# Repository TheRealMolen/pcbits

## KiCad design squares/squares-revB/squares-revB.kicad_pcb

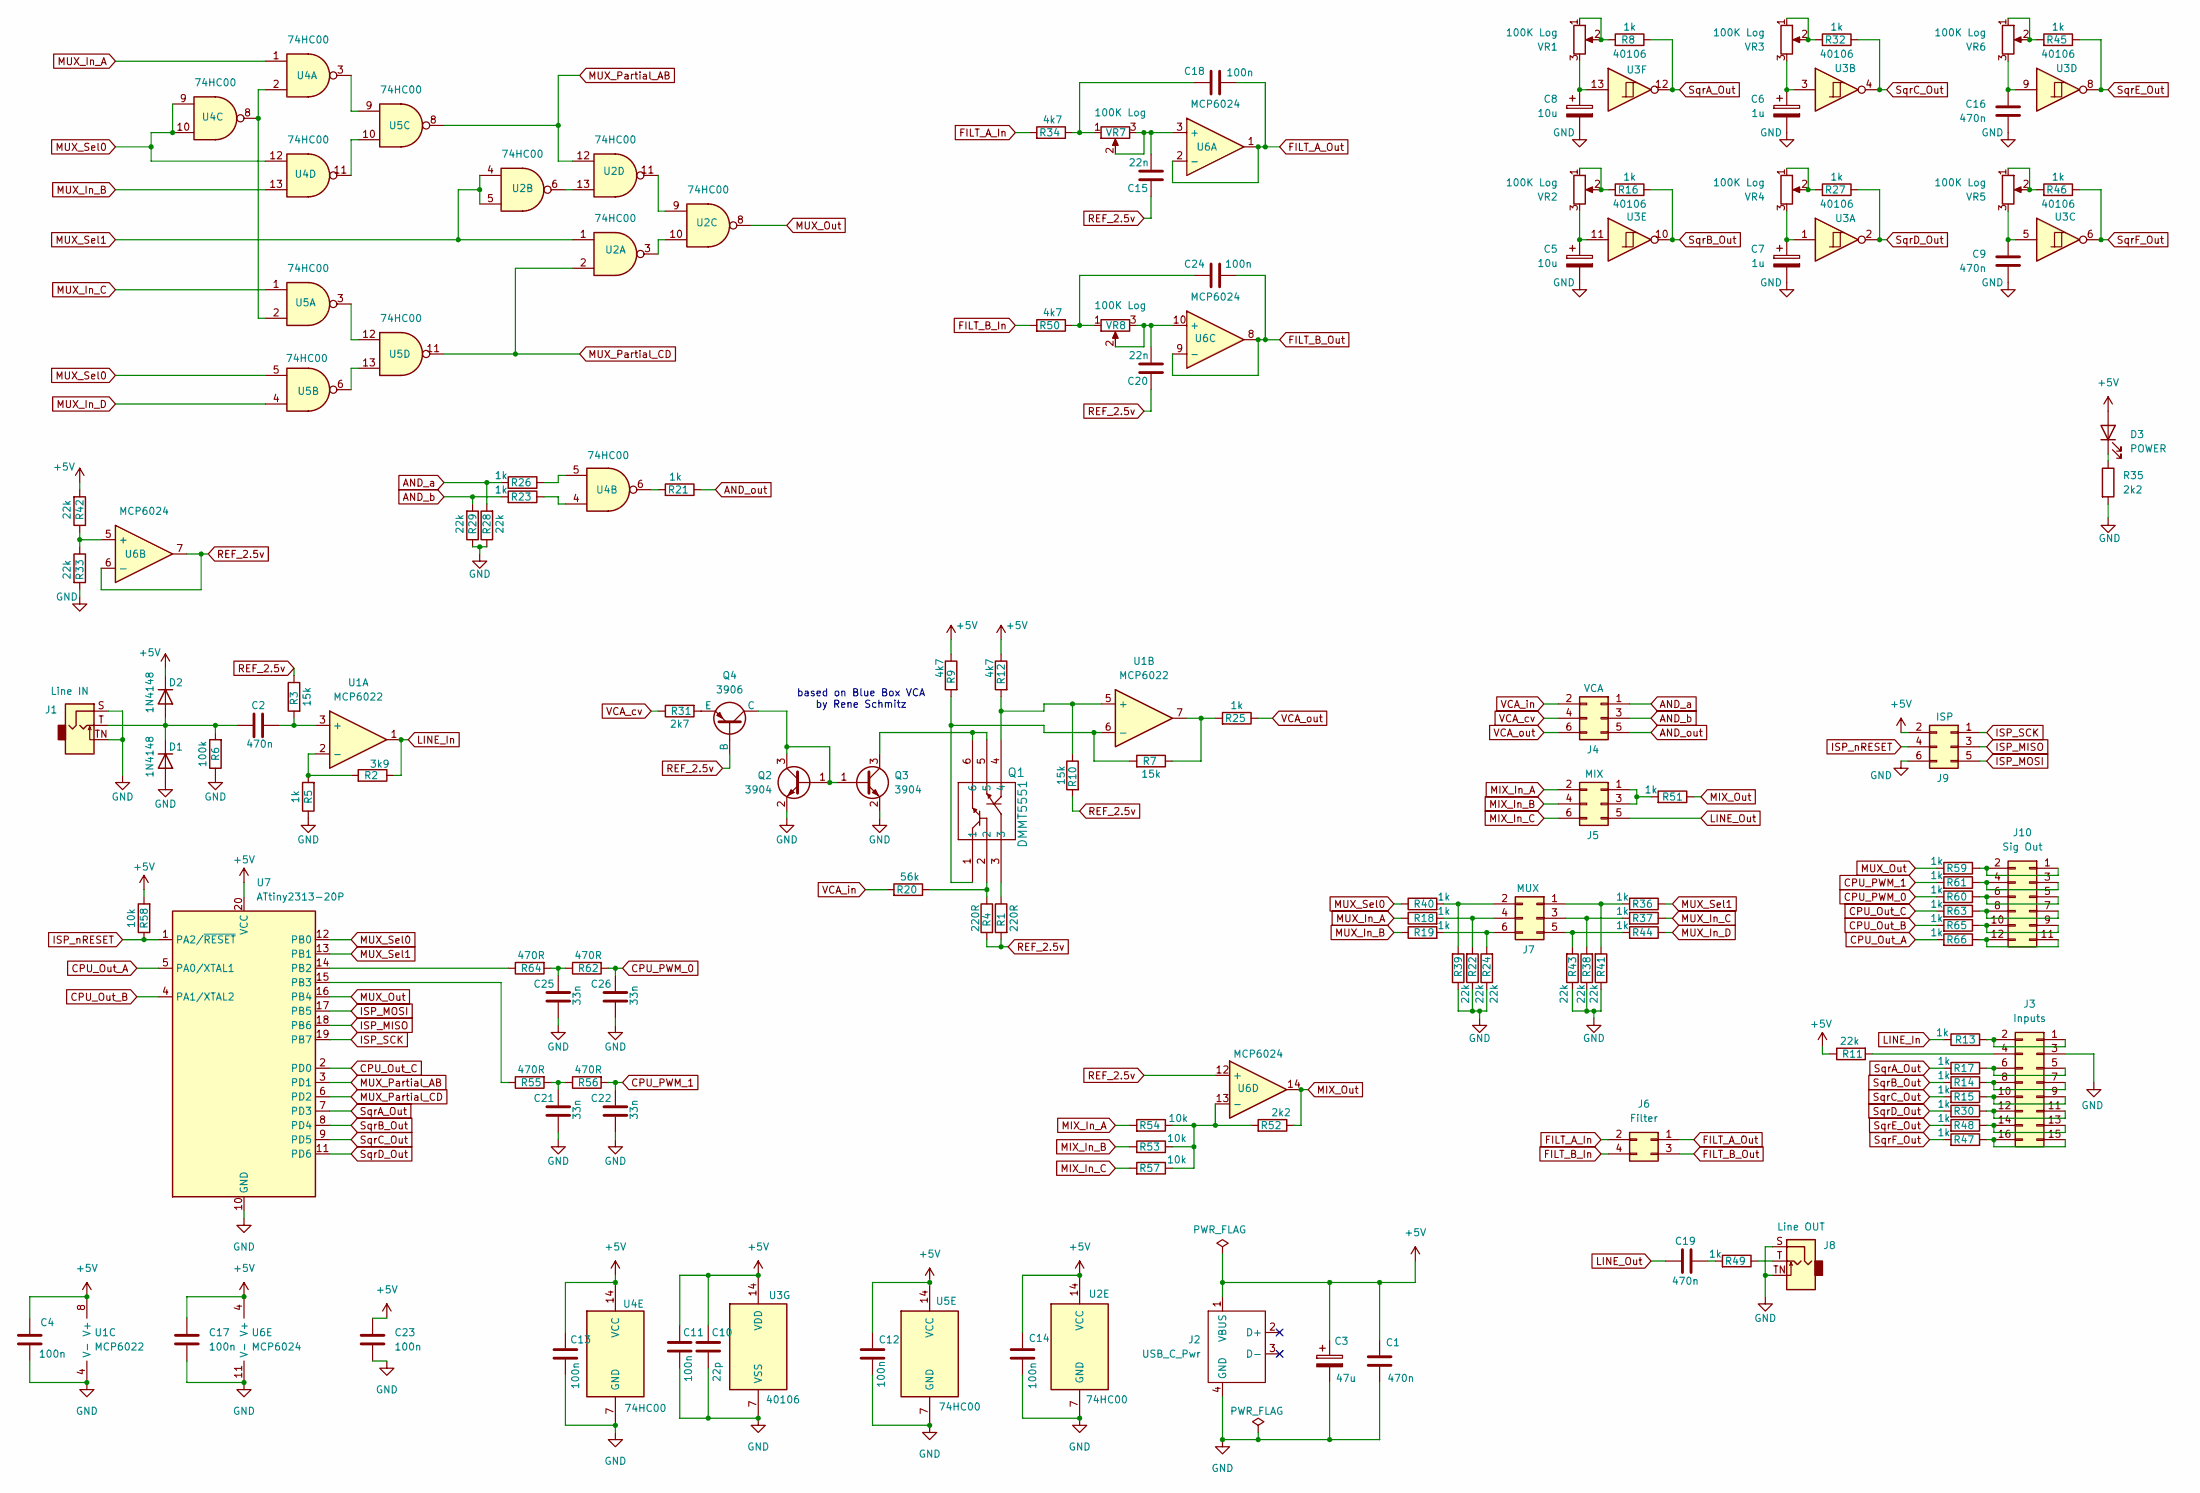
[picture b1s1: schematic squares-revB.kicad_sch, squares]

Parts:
C1, C2, C19: 470n; C_Rect_L7.0mm_W3.5mm_P5.00mm
C3: 47u; CP_Radial_D5.0mm_P2.50mm
C4, C11, C12, C13, C14, C17, C18, C23, C24: 100n; C_0805_2012Metric_Pad1.18x1.45mm_HandSolder
C5, C8: 10u; CP_Radial_D5.0mm_P2.50mm
C6, C7: 1u; CP_Radial_D5.0mm_P2.50mm
C9, C16: 470n; C_0805_2012Metric_Pad1.18x1.45mm_HandSolder
C10: 22p; C_0805_2012Metric_Pad1.18x1.45mm_HandSolder
C15, C20: 22n; C_0805_2012Metric_Pad1.18x1.45mm_HandSolder
C21, C22, C25, C26: 33n; C_0805_2012Metric_Pad1.18x1.45mm_HandSolder
D1, D2: 1N4148; D_1206_3216Metric_Pad1.42x1.75mm_HandSolder
D3: POWER; LED_0805_2012Metric_Pad1.15x1.40mm_HandSolder
J1: Line IN; Jack_3.5mm_QingPu_WQP-PJ398SM_Vertical
J2: USB_C_Pwr; USB-C_Module_RUNCCI-YUN
J3: Inputs; PinSocket_2x08_P2.54mm_Vertical
J4: VCA; PinSocket_2x03_P2.54mm_Vertical
J5: MIX; PinSocket_2x03_P2.54mm_Vertical
J6: Filter; PinSocket_2x02_P2.54mm_Vertical
J7: MUX; PinSocket_2x03_P2.54mm_Vertical
J8: Line OUT; Jack_3.5mm_QingPu_WQP-PJ398SM_Vertical
J9: ISP; PinSocket_2x03_P2.54mm_Vertical
J10: Sig Out; PinSocket_2x06_P2.54mm_Vertical
Q1: DMMT5551; SOIC6_DMMT551_DIO
Q2, Q3: 3904; SOT-23
Q4: 3906; SOT-23
R1, R4: 220R; R_0805_2012Metric_Pad1.20x1.40mm_HandSolder
R2: 3k9; R_0805_2012Metric_Pad1.20x1.40mm_HandSolder
R3, R7, R10: 15k; R_0805_2012Metric_Pad1.20x1.40mm_HandSolder
R5, R8, R13, R14, R15, R16, R17, R18, R19, R21, R23, R25, R26, R27, R30, R32, R36, R37, R40, R44, R45, R46, R47, R48, R49, R51, R59, R60, R61, R63, R65, R66: 1k; R_0805_2012Metric_Pad1.20x1.40mm_HandSolder
R6: 100k; R_0805_2012Metric_Pad1.20x1.40mm_HandSolder
R9, R12, R34, R50: 4k7; R_0805_2012Metric_Pad1.20x1.40mm_HandSolder
R11, R22, R24, R28, R29, R33, R38, R39, R41, R42, R43: 22k; R_0805_2012Metric_Pad1.20x1.40mm_HandSolder
R20: 56k; R_0805_2012Metric_Pad1.20x1.40mm_HandSolder
R31: 2k7; R_0805_2012Metric_Pad1.20x1.40mm_HandSolder
R35, R52: 2k2; R_0805_2012Metric_Pad1.20x1.40mm_HandSolder
R53, R54, R57, R58: 10k; R_0805_2012Metric_Pad1.20x1.40mm_HandSolder
R55, R56, R62, R64: 470R; R_0805_2012Metric_Pad1.20x1.40mm_HandSolder
U1: MCP6022; DIP-8_W7.62mm
U2, U4, U5: 74HC00; TSSOP-14_4.4x5mm_P0.65mm
U3: 40106; DIP-14_W7.62mm
U6: MCP6024; DIP-14_W7.62mm
U7: ATtiny2313-20P; DIP-20_W7.62mm_Socket
VR1, VR2, VR3, VR4, VR5, VR6, VR7, VR8: 100K Log; Potentiometer_Alpha_RD901F-40-00D_Single_Vertical

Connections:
+5V: C1.1, C3.1, C4.1, C10.1, C11.1, C12.1, C13.1, C14.1, C17.1, C23.1, D2.1 (K), D3.2 (A), J2.1 (VBUS), J9.2, R9.1, R11.1, R12.1, R42.2, R58.2, U1.8 (V+), U2.14 (VCC), U3.14 (VDD), U4.14 (VCC), U5.14 (VCC), U6.4 (V+), U7.20 (VCC)
AND_a: J4.1, R26.2, R28.2
AND_b: J4.3, R23.2, R29.2
AND_out: J4.5, R21.1
CPU_Out_A: R66.2, U7.5 (PA0/XTAL1)
CPU_Out_B: R65.2, U7.4 (PA1/XTAL2)
CPU_Out_C: R63.2, U7.2 (PD0)
CPU_PWM_0: C26.2, R60.2, R62.2
CPU_PWM_1: C22.2, R56.2, R61.2
FILT_A_In: J6.2, R34.2
FILT_A_Out: C18.2, J6.1, U6.1, U6.2 (-)
FILT_B_In: J6.4, R50.2
FILT_B_Out: C24.2, J6.3, U6.8, U6.9 (-)
GND: C1.2, C3.2, C4.2, C5.2, C6.2, C7.2, C8.2, C9.1, C10.2, C11.2, C12.2, C13.2, C14.2, C16.1, C17.2, C21.1, C22.1, C23.2, C25.1, C26.1, D1.2 (A), J1.S, J1.TN, J2.4 (GND), J3.3, J8.S, J8.TN, J9.6, Q2.2 (E), Q3.2 (E), R5.1, R6.1, R22.1, R24.1, R28.1, R29.1, R33.2, R35.2, R38.1, R39.1, R41.1, R43.1, U1.4 (V-), U2.7 (GND), U3.7 (VSS), U4.7 (GND), U5.7 (GND), U6.11 (V-), U7.10 (GND)
ISP_MISO: J9.3, U7.18 (PB6)
ISP_MOSI: J9.5, U7.17 (PB5)
ISP_SCK: J9.1, U7.19 (PB7)
ISP_nRESET: J9.4, R58.1, U7.1 (PA2/~RESET)
LINE_In: R2.1, R13.1, U1.1
LINE_Out: C19.1, J5.5
MIX_In_A: J5.2, R54.2
MIX_In_B: J5.4, R53.2
MIX_In_C: J5.6, R57.2
MIX_Out: R51.1, R52.1, U6.14
MUX_In_A: R18.1, U4.1
MUX_In_B: R19.1, U4.13
MUX_In_C: R37.1, U5.1
MUX_In_D: R44.1, U5.4
MUX_Out: R59.2, U2.8, U7.16 (PB4)
MUX_Partial_AB: U2.12, U5.8, U7.3 (PD1)
MUX_Partial_CD: U2.2, U5.11, U7.6 (PD2)
MUX_Sel0: R40.1, U4.9, U4.10, U4.12, U5.5, U7.12 (PB0)
MUX_Sel1: R36.1, U2.1, U2.4, U2.5, U7.13 (PB1)
unnamed: C5.1, U3.11, VR2.3
unnamed: C6.1, U3.3, VR3.3
unnamed: C7.1, U3.1, VR4.3
unnamed: C8.1, U3.13, VR1.3
unnamed: C9.2, U3.5, VR5.3
unnamed: C16.2, U3.9, VR6.3
unnamed: C18.1, R34.1, VR7.1
unnamed: C19.2, R49.2
unnamed: C21.2, R55.2, R56.1
unnamed: C24.1, R50.1, VR8.1
unnamed: C25.2, R62.1, R64.2
unnamed: C2.1, D1.1 (K), D2.2 (A), J1.T, R6.2
unnamed: D3.1 (K), R35.1
unnamed: J3.1, J3.2, R13.2
unnamed: J3.4, R11.2
unnamed: J3.5, J3.6, R17.1
unnamed: J3.7, J3.8, R14.1
unnamed: J3.9, J3.10, R15.1
unnamed: J3.11, J3.12, R30.1
unnamed: J3.13, J3.14, R48.1
unnamed: J3.15, J3.16, R47.1
unnamed: J5.1, J5.3, R51.2
unnamed: J7.1, R36.2, R41.2
unnamed: J7.2, R39.2, R40.2
unnamed: J7.3, R37.2, R38.2
unnamed: J7.4, R18.2, R22.2
unnamed: J7.5, R43.2, R44.2
unnamed: J7.6, R19.2, R24.2
unnamed: J8.T, R49.1
unnamed: J10.1, J10.2, R59.1
unnamed: J10.3, J10.4, R61.1
unnamed: J10.5, J10.6, R60.1
unnamed: J10.7, J10.8, R63.1
unnamed: J10.9, J10.10, R65.1
unnamed: J10.11, J10.12, R66.1
unnamed: Q1.2, R4.1, R20.1
unnamed: Q1.3, R1.1
unnamed: Q2.1 (B), Q2.3 (C), Q3.1 (B), Q4.1 (C)
unnamed: Q1.5, Q1.6, Q3.3 (C)
unnamed: Q4.3 (E), R31.2
unnamed: R8.2, VR1.1, VR1.2
unnamed: R16.2, VR2.1, VR2.2
unnamed: R21.2, U4.6
unnamed: R23.1, U4.4
unnamed: R7.1, R25.2, U1.7
unnamed: R26.1, U4.5
unnamed: R27.2, VR4.1, VR4.2
unnamed: R32.2, VR3.1, VR3.2
unnamed: R45.2, VR6.1, VR6.2
unnamed: R46.2, VR5.1, VR5.2
unnamed: C2.2, R3.2, U1.3 (+)
unnamed: R2.2, R5.2, U1.2 (-)
unnamed: Q1.4, R10.1, R12.2, U1.5 (+)
unnamed: Q1.1, R7.2, R9.2, U1.6 (-)
unnamed: U2.3, U2.10
unnamed: U2.9, U2.11
unnamed: U2.6, U2.13
unnamed: U4.2, U4.8, U5.2
unnamed: U4.3, U5.9
unnamed: U4.11, U5.10
unnamed: U5.3, U5.12
unnamed: U5.6, U5.13
unnamed: C15.2, U6.3 (+), VR7.2, VR7.3
unnamed: R33.1, R42.1, U6.5 (+)
unnamed: C20.2, U6.10 (+), VR8.2, VR8.3
unnamed: R52.2, R53.1, R54.1, R57.1, U6.13 (-)
unnamed: R64.1, U7.14 (PB2)
unnamed: R55.1, U7.15 (PB3)
REF_2.5v: C15.1, C20.1, Q4.2 (B), R1.2, R3.1, R4.2, R10.2, U6.6 (-), U6.7, U6.12 (+)
SqrA_Out: R8.1, R17.2, U3.12, U7.7 (PD3)
SqrB_Out: R14.2, R16.1, U3.10, U7.8 (PD4)
SqrC_Out: R15.2, R32.1, U3.4, U7.9 (PD5)
SqrD_Out: R27.1, R30.2, U3.2, U7.11 (PD6)
SqrE_Out: R45.1, R48.2, U3.8
SqrF_Out: R46.1, R47.2, U3.6
VCA_cv: J4.4, R31.1
VCA_in: J4.2, R20.2
VCA_out: J4.6, R25.1

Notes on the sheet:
based on Blue Box VCA by Rene Schmitz

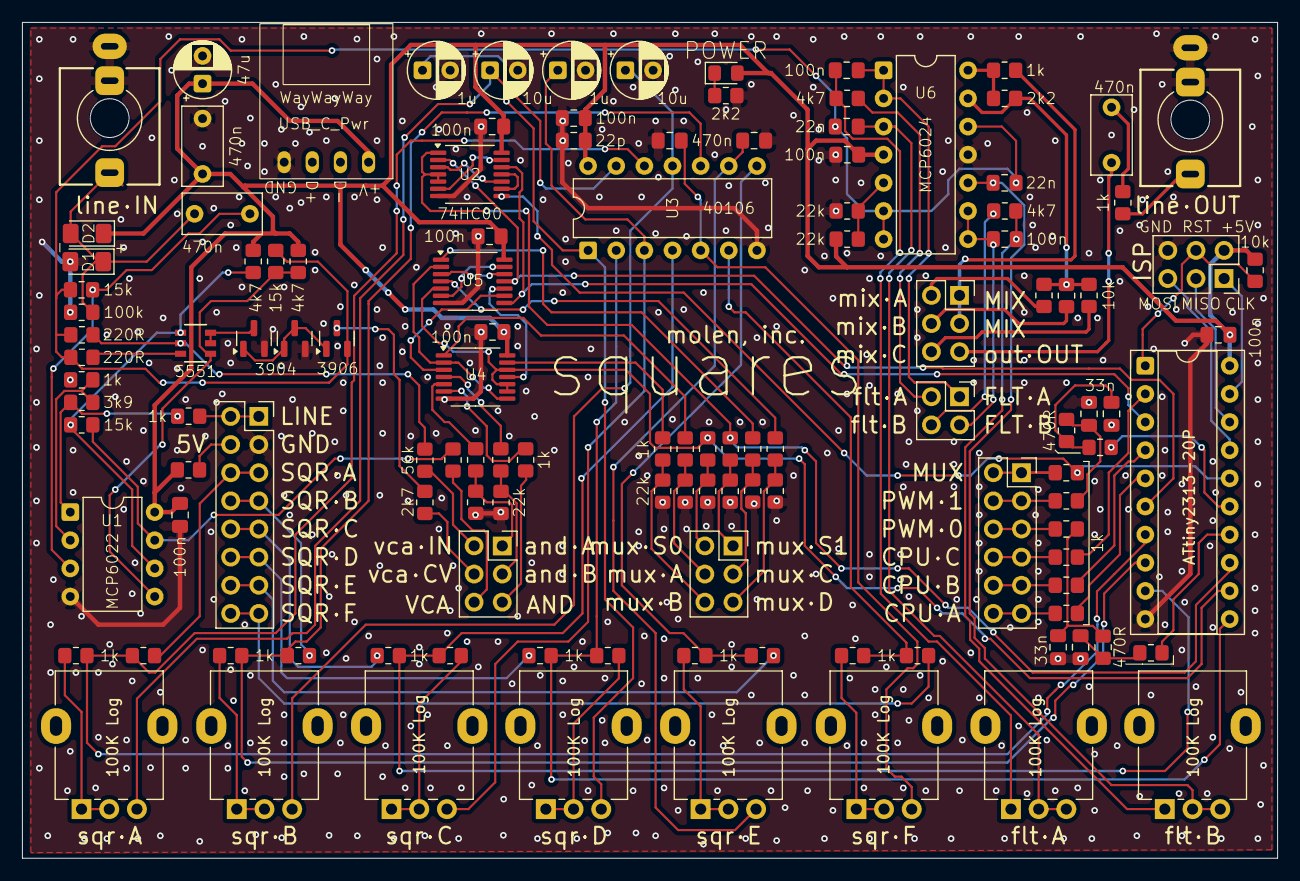
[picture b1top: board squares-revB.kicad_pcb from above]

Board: 2 copper layers, 113.3 x 75.4 mm, 124 parts (0 on the bottom side), 111 nets.

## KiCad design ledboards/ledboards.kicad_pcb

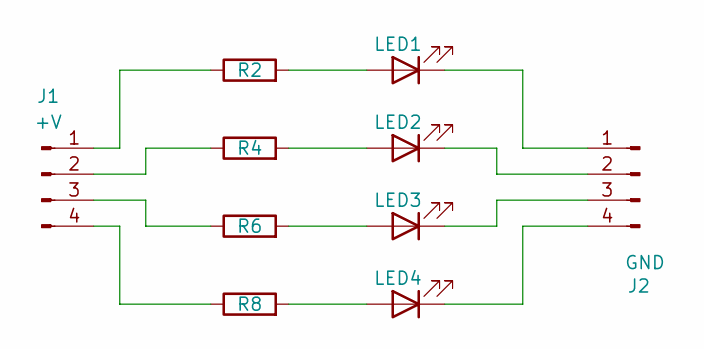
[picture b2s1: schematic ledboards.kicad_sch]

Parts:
J1: +V; PinHeader_1x04_P2.54mm_Vertical
J2: GND; PinHeader_1x04_P2.54mm_Vertical
LED1, LED2, LED3, LED4: LED_0805_2012Metric_Pad1.15x1.40mm_HandSolder
R2, R4, R6, R8: R_0805_2012Metric_Pad1.20x1.40mm_HandSolder

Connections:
unnamed: J1.1, R2.1
unnamed: J1.2, R4.1
unnamed: J1.3, R6.1
unnamed: J1.4, R8.1
unnamed: J2.1, LED1.1 (K)
unnamed: J2.2, LED2.1 (K)
unnamed: J2.3, LED3.1 (K)
unnamed: J2.4, LED4.1 (K)
unnamed: LED1.2 (A), R2.2
unnamed: LED2.2 (A), R4.2
unnamed: LED3.2 (A), R6.2
unnamed: LED4.2 (A), R8.2

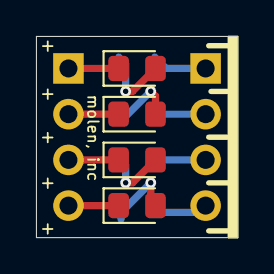
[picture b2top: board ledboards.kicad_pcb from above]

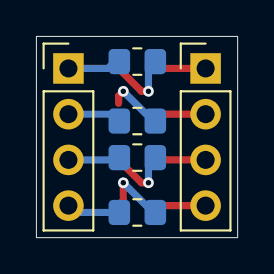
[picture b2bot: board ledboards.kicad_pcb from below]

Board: 2 copper layers, 11.2 x 11.2 mm, 10 parts (6 on the bottom side), 12 nets.

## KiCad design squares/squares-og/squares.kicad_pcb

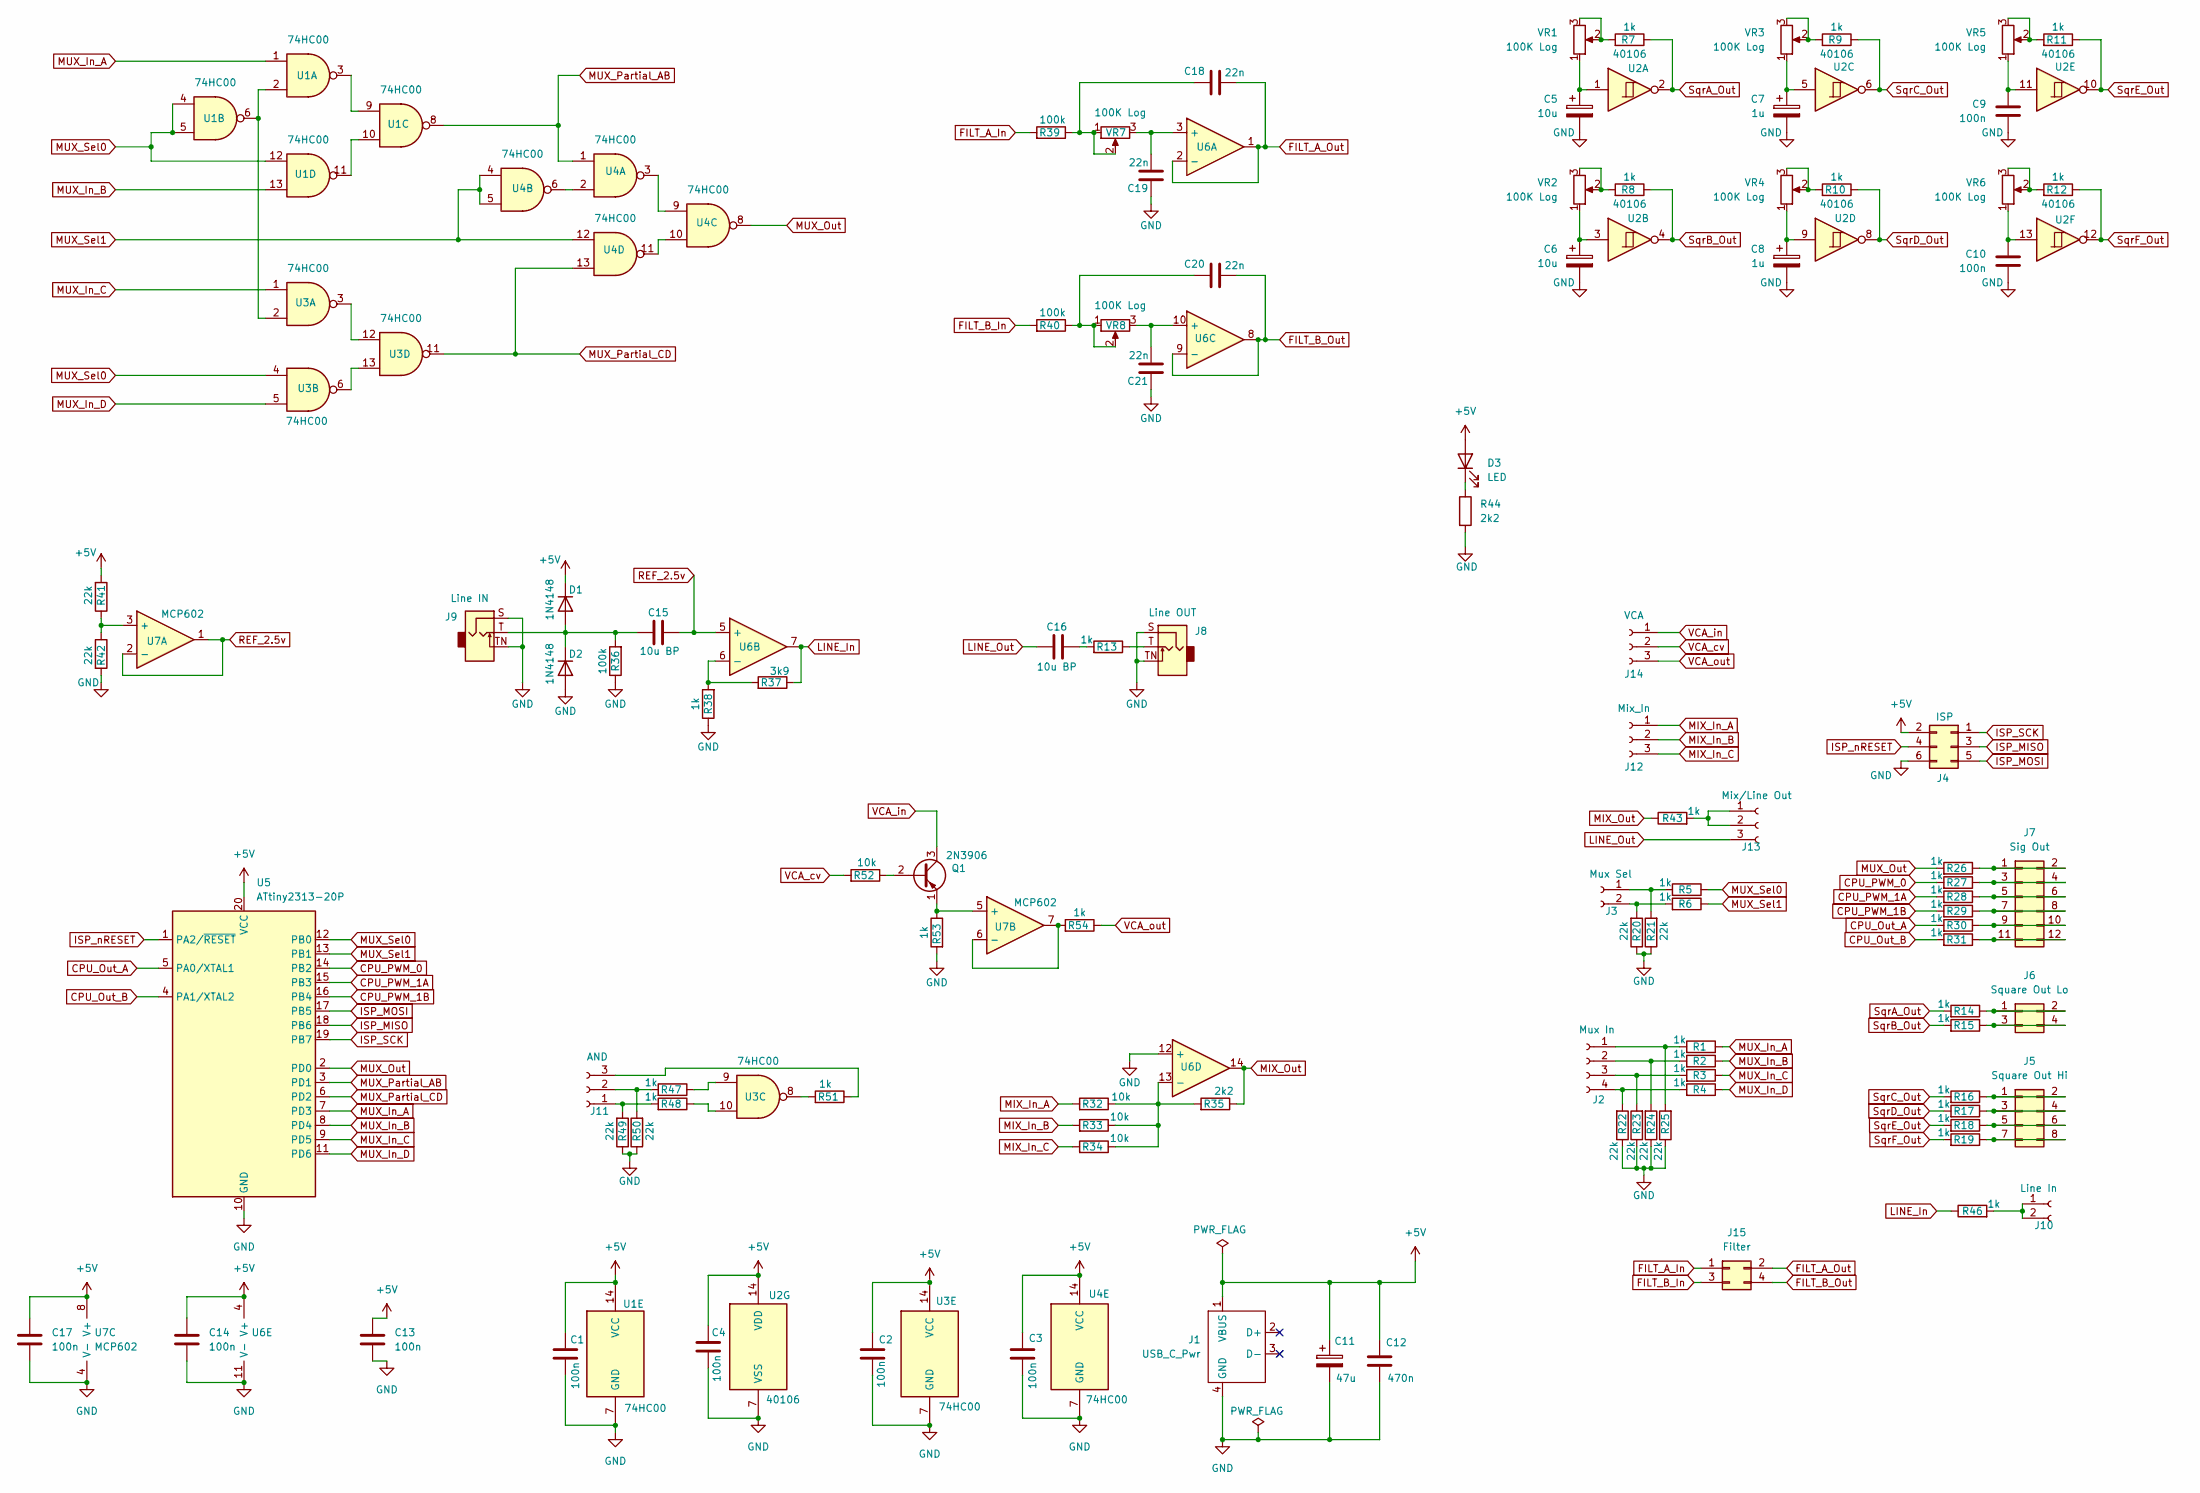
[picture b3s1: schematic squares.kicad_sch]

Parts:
C1, C2, C3, C4, C9, C10, C13, C14, C17: 100n; C_0805_2012Metric_Pad1.18x1.45mm_HandSolder
C5, C6: 10u; CP_Radial_D5.0mm_P2.50mm
C7, C8: 1u; CP_Radial_D5.0mm_P2.50mm
C11: 47u; CP_Radial_D5.0mm_P2.50mm
C12: 470n; C_Rect_L7.0mm_W3.5mm_P5.00mm
C15, C16: 10u BP; CP_Radial_D5.0mm_P2.00mm
C18, C19, C20, C21: 22n; C_0805_2012Metric_Pad1.18x1.45mm_HandSolder
D1, D2: 1N4148; D_1206_3216Metric_Pad1.42x1.75mm_HandSolder
D3: LED; LED_0805_2012Metric_Pad1.15x1.40mm_HandSolder
J1: USB_C_Pwr; USB-C_Module_RUNCCI-YUN
J2: Mux In; PinSocket_1x04_P2.54mm_Vertical
J3: Mux Sel; PinSocket_1x02_P2.54mm_Vertical
J4: ISP; PinSocket_2x03_P2.54mm_Vertical
J5: Square Out Hi; PinSocket_2x04_P2.54mm_Vertical
J6: Square Out Lo; PinSocket_2x02_P2.54mm_Vertical
J7: Sig Out; PinSocket_2x06_P2.54mm_Vertical
J8: Line OUT; Jack_3.5mm_QingPu_WQP-PJ398SM_Vertical
J9: Line IN; Jack_3.5mm_QingPu_WQP-PJ398SM_Vertical
J10: Line In; PinSocket_1x02_P2.54mm_Vertical
J11: AND; PinSocket_1x03_P2.54mm_Vertical
J12: Mix_In; PinSocket_1x03_P2.54mm_Vertical
J13: Mix/Line Out; PinSocket_1x03_P2.54mm_Vertical
J14: VCA; PinSocket_1x03_P2.54mm_Vertical
J15: Filter; PinSocket_2x02_P2.54mm_Vertical
Q1: 2N3906; TO-92_Inline
R1, R2, R3, R4, R5, R6, R7, R8, R9, R10, R11, R12, R13, R14, R15, R16, R17, R18, R19, R26, R27, R28, R29, R30, R31, R38, R43, R46, R47, R48, R51, R53, R54: 1k; R_0805_2012Metric_Pad1.20x1.40mm_HandSolder
R20, R21, R22, R23, R24, R25, R41, R42, R49, R50: 22k; R_0805_2012Metric_Pad1.20x1.40mm_HandSolder
R32, R33, R34, R52: 10k; R_0805_2012Metric_Pad1.20x1.40mm_HandSolder
R35, R44: 2k2; R_0805_2012Metric_Pad1.20x1.40mm_HandSolder
R36, R39, R40: 100k; R_0805_2012Metric_Pad1.20x1.40mm_HandSolder
R37: 3k9; R_0805_2012Metric_Pad1.20x1.40mm_HandSolder
U1, U3, U4: 74HC00; TSSOP-14_4.4x5mm_P0.65mm
U2: 40106; DIP-14_W7.62mm
U5: ATtiny2313-20P; DIP-20_W7.62mm_Socket
U6: DIP-14_W7.62mm
U7: MCP602; DIP-8_W7.62mm
VR1, VR2, VR3, VR4, VR5, VR6, VR7, VR8: 100K Log; Potentiometer_Alpha_RD901F-40-00D_Single_Vertical_CircularH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

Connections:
+5V: C1.1, C2.1, C3.1, C4.1, C11.1, C12.1, C13.1, C14.1, C17.1, D1.1 (K), D3.2 (A), J1.1 (VBUS), J4.2, R41.2, U1.14 (VCC), U2.14 (VDD), U3.14 (VCC), U4.14 (VCC), U5.20 (VCC), U6.4 (V+), U7.8 (V+)
CPU_Out_A: R30.2, U5.5 (PA0/XTAL1)
CPU_Out_B: R31.2, U5.4 (PA1/XTAL2)
CPU_PWM_0: R27.2, U5.14 (PB2)
CPU_PWM_1A: R28.2, U5.15 (PB3)
CPU_PWM_1B: R29.2, U5.16 (PB4)
FILT_A_In: J15.1, R39.2
FILT_A_Out: C18.2, J15.2, U6.1, U6.2 (-)
FILT_B_In: J15.3, R40.2
FILT_B_Out: C20.2, J15.4, U6.8, U6.9 (-)
GND: C1.2, C2.2, C3.2, C4.2, C5.2, C6.2, C7.2, C8.2, C9.1, C10.1, C11.2, C12.2, C13.2, C14.2, C17.2, C19.1, C21.1, D2.2 (A), J1.4 (GND), J4.6, J8.S, J8.TN, J9.S, J9.TN, R20.1, R21.1, R22.1, R23.1, R24.1, R25.1, R36.1, R38.1, R42.2, R44.2, R49.1, R50.1, R53.2, U1.7 (GND), U2.7 (VSS), U3.7 (GND), U4.7 (GND), U5.10 (GND), U6.11 (V-), U6.12 (+), U7.4 (V-)
ISP_MISO: J4.3, U5.18 (PB6)
ISP_MOSI: J4.5, U5.17 (PB5)
ISP_SCK: J4.1, U5.19 (PB7)
ISP_nRESET: J4.4, U5.1 (PA2/~RESET)
LINE_In: R37.1, R46.1, U6.7
LINE_Out: C16.1, J13.3
MIX_In_A: J12.1, R32.2
MIX_In_B: J12.2, R33.2
MIX_In_C: J12.3, R34.2
MIX_Out: R35.1, R43.1, U6.14
MUX_In_A: R1.1, U1.1, U5.7 (PD3)
MUX_In_B: R2.1, U1.13, U5.8 (PD4)
MUX_In_C: R3.1, U3.1, U5.9 (PD5)
MUX_In_D: R4.1, U3.5, U5.11 (PD6)
MUX_Out: R26.2, U4.8, U5.2 (PD0)
MUX_Partial_AB: U1.8, U4.1, U5.3 (PD1)
MUX_Partial_CD: U3.11, U4.13, U5.6 (PD2)
MUX_Sel0: R5.1, U1.4, U1.5, U1.12, U3.4, U5.12 (PB0)
MUX_Sel1: R6.1, U4.4, U4.5, U4.12, U5.13 (PB1)
unnamed: C5.1, U2.1, VR1.1
unnamed: C6.1, U2.3, VR2.1
unnamed: C7.1, U2.5, VR3.1
unnamed: C8.1, U2.9, VR4.1
unnamed: C9.2, U2.11, VR5.1
unnamed: C10.2, U2.13, VR6.1
unnamed: C16.2, R13.2
unnamed: C18.1, R39.1, VR7.1, VR7.2
unnamed: C20.1, R40.1, VR8.1, VR8.2
unnamed: C15.1, D1.2 (A), D2.1 (K), J9.T, R36.2
unnamed: D3.1 (K), R44.1
unnamed: J2.1, R1.2, R25.2
unnamed: J2.2, R2.2, R24.2
unnamed: J2.3, R3.2, R23.2
unnamed: J2.4, R4.2, R22.2
unnamed: J3.1, R5.2, R21.2
unnamed: J3.2, R6.2, R20.2
unnamed: J5.1, J5.2, R16.1
unnamed: J5.3, J5.4, R17.1
unnamed: J5.5, J5.6, R18.1
unnamed: J5.7, J5.8, R19.1
unnamed: J6.1, J6.2, R14.1
unnamed: J6.3, J6.4, R15.1
unnamed: J7.1, J7.2, R26.1
unnamed: J7.3, J7.4, R27.1
unnamed: J7.5, J7.6, R28.1
unnamed: J7.7, J7.8, R29.1
unnamed: J7.9, J7.10, R30.1
unnamed: J7.11, J7.12, R31.1
unnamed: J8.T, R13.1
unnamed: J10.1, J10.2, R46.2
unnamed: J11.1, R48.2, R49.2
unnamed: J11.2, R47.2, R50.2
unnamed: J11.3, R51.1
unnamed: J13.1, J13.2, R43.2
unnamed: Q1.2 (B), R52.1
unnamed: Q1.1 (E), R53.1, U7.5 (+)
unnamed: R7.2, VR1.2, VR1.3
unnamed: R8.2, VR2.2, VR2.3
unnamed: R9.2, VR3.2, VR3.3
unnamed: R10.2, VR4.2, VR4.3
unnamed: R11.2, VR5.2, VR5.3
unnamed: R12.2, VR6.2, VR6.3
unnamed: R47.1, U3.9
unnamed: R48.1, U3.10
unnamed: R51.2, U3.8
unnamed: U1.2, U1.6, U3.2
unnamed: U1.3, U1.9
unnamed: U1.10, U1.11
unnamed: U3.3, U3.12
unnamed: U3.6, U3.13
unnamed: U4.2, U4.6
unnamed: U4.3, U4.9
unnamed: U4.10, U4.11
unnamed: C19.2, U6.3 (+), VR7.3
unnamed: R37.2, R38.2, U6.6 (-)
unnamed: C21.2, U6.10 (+), VR8.3
unnamed: R32.1, R33.1, R34.1, R35.2, U6.13 (-)
unnamed: R41.1, R42.1, U7.3 (+)
unnamed: R54.2, U7.6 (-), U7.7
REF_2.5v: C15.2, U6.5 (+), U7.1, U7.2 (-)
SqrA_Out: R7.1, R14.2, U2.2
SqrB_Out: R8.1, R15.2, U2.4
SqrC_Out: R9.1, R16.2, U2.6
SqrD_Out: R10.1, R17.2, U2.8
SqrE_Out: R11.1, R18.2, U2.10
SqrF_Out: R12.1, R19.2, U2.12
VCA_cv: J14.2, R52.2
VCA_in: J14.1, Q1.3 (C)
VCA_out: J14.3, R54.1

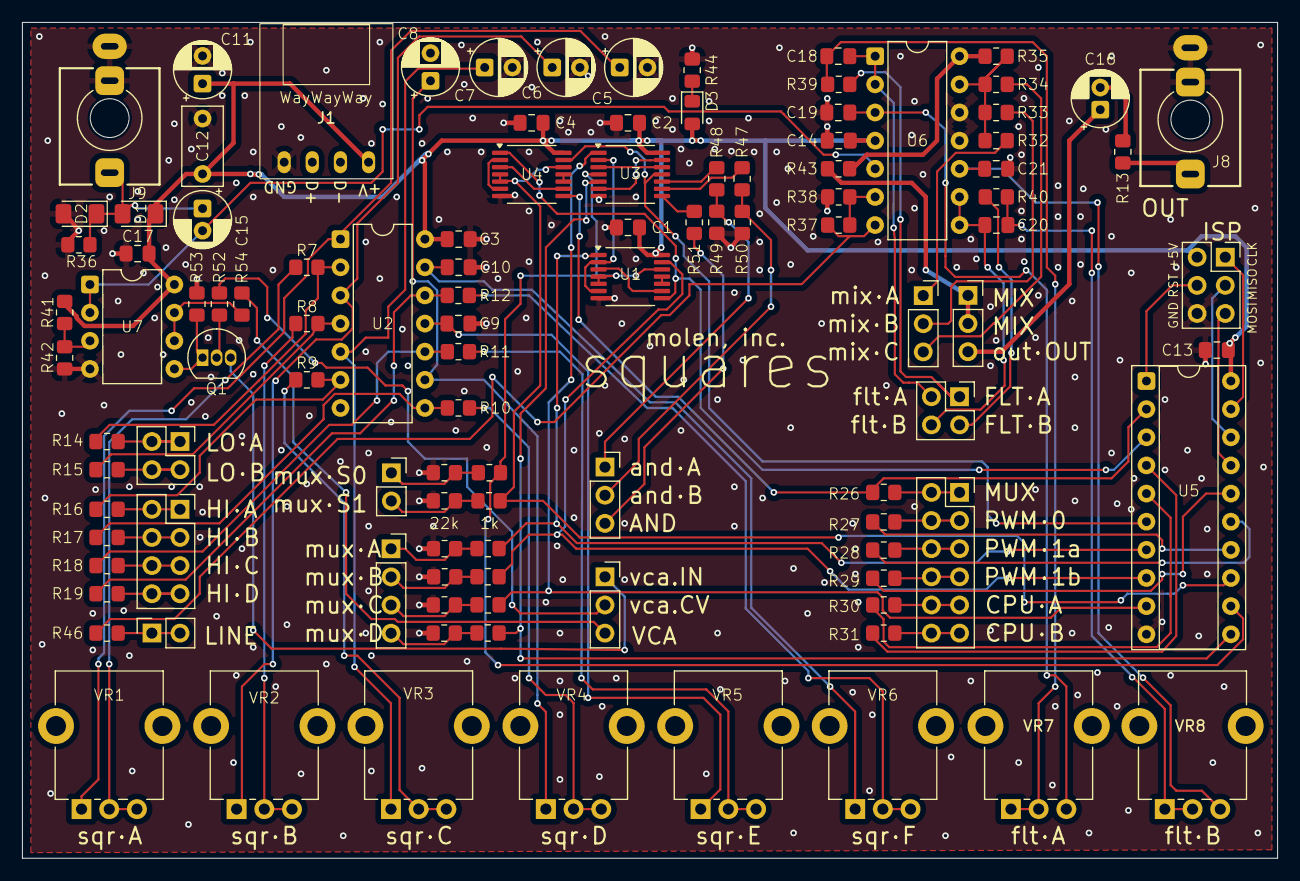
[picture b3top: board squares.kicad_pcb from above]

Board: 2 copper layers, 113.3 x 75.4 mm, 108 parts (0 on the bottom side), 100 nets.

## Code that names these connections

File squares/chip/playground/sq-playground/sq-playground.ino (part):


// all squares boards have the following wired to ISP header
//  RESET ->  PA2 | /RESET
//  MOSI  ->  PB5
//  MISO  ->  PB6
//  SCK   ->  PB7

#define SQR_REV_A 1
#define SQR_REV_B (1 - SQR_REV_A)

#if SQR_REV_A
// squares revA board has the following hardwired:
//  CPU_Out_A -> PA0
//  CPU_Out_B -> PA1
//  MUX_Sel0 -> PB0 | PCINT0
//  MUX_Sel1 -> PB1 | PCINT1
//  CPU_PWM_0 -> PB2 | OC0A (timer0 pwm out) | PCINT2 (pin change interrupt source)
//  CPU_PWM_1A-> PB3 | OC1A (timer1 pwmA out) | PCINT3
//  [unsupported] CPU_Out_C -> PB4 | OC1B (timer1 pwmB out) | PCINT4
//  MUX_Out -> PD0
//  MUX_Partial_AB -> PD1
//  MUX_Partial_CD -> PD2 | INT0 (external interrupt source)
//  MUX_In_A -> PD3 | INT1 (external interrupt source)
//  MUX_In_B -> PD4 | T0 (timer0 external clock)
//  MUX_In_C -> PD5 | T1 (timer1 external clock) or OC0B (timer0 pwm out++)
//  MUX_In_D -> PD6 | ICP (timer1 input capture pin)

constexpr byte Pin_CPU_Out_A  = PIN_PA0;
constexpr byte Pin_CPU_Out_B  = PIN_PA1;
constexpr byte Pin_MUX_Sel0   = PIN_PB0;
constexpr byte Pin_MUX_Sel1   = PIN_PB1;
constexpr byte Pin_CPU_PWM_A  = PIN_PB2;
constexpr byte Pin_CPU_PWM_B  = PIN_PB3;
constexpr byte Pin_MUX_Out    = PIN_PD0;
constexpr byte Pin_Partial_AB = PIN_PD1;
constexpr byte Pin_Partial_CD = PIN_PD2;
constexpr byte Pin_MUX_In_A   = PIN_PD3;
constexpr byte Pin_MUX_In_B   = PIN_PD4;
constexpr byte Pin_MUX_In_C   = PIN_PD5;
constexpr byte Pin_MUX_In_D   = PIN_PD6;

// to simplify code...
constexpr byte Pin_SqrA_In = Pin_MUX_In_A;
constexpr byte Pin_SqrB_In = Pin_MUX_In_B;
constexpr byte Pin_SqrC_In = Pin_MUX_In_C;
constexpr byte Pin_SqrD_In = Pin_MUX_In_D;

#elif SQR_REV_B
// squares revB board has the following hardwired:
//  CPU_Out_A -> PA0
//  CPU_Out_B -> PA1
//  MUX_Sel0 -> PB0 | PCINT0
//  MUX_Sel1 -> PB1 | PCINT1
//  CPU_PWM_A -> PB2 | OC0A (timer0 pwm out) | PCINT2 (pin change interrupt source)
//  CPU_PWM_B -> PB3 | OC1A (timer1 pwmA out) | PCINT3
//  MUX_Out -> PB4 | OC1B (timer1 pwmB out) | PCINT4
//  CPU_Out_C -> PD0
//  MUX_Partial_AB -> PD1
//  MUX_Partial_CD -> PD2 | INT0 (external interrupt source)
//  SqrA_Out -> PD3 | INT1 (external interrupt source)
//  SqrB_Out -> PD4 | T0 (timer0 external clock)
//  SqrC_Out -> PD5 | T1 (timer1 external clock) or OC0B (timer0 pwm out++)
//  SqrD_Out -> PD6 | ICP (timer1 input capture pin)

constexpr byte Pin_CPU_Out_A  = PIN_PA0;
constexpr byte Pin_CPU_Out_B  = PIN_PA1;
constexpr byte Pin_MUX_Sel0   = PIN_PB0;
constexpr byte Pin_MUX_Sel1   = PIN_PB1;
constexpr byte Pin_CPU_PWM_A  = PIN_PB2;
constexpr byte Pin_CPU_PWM_B  = PIN_PB3;
constexpr byte Pin_MUX_Out    = PIN_PB4;  // NOTE: swapped from revA vvv
constexpr byte Pin_CPU_Out_C  = PIN_PD0;  // NOTE: swapped from revA ^^^
constexpr byte Pin_Partial_AB = PIN_PD1;
constexpr byte Pin_Partial_CD = PIN_PD2;
constexpr byte Pin_SqrA_In    = PIN_PD3;
constexpr byte Pin_SqrB_In    = PIN_PD4;
constexpr byte Pin_SqrC_In    = PIN_PD5;
constexpr byte Pin_SqrD_In    = PIN_PD6;

constexpr byte BitD_CPU_Out_C = 0;
constexpr byte MskD_CPU_Out_C = 1 << BitD_CPU_Out_C;
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constexpr byte MskD_SqrC_In = 1 << BitD_SqrC_In;
constexpr byte MskD_SqrD_In = 1 << BitD_SqrD_In;

static_assert(Pin_MUX_Sel1 == PIN_PB1);
constexpr byte BitB_MUX_Sel1 = 1;
constexpr byte MskB_MUX_Sel1 = 1 << BitB_MUX_Sel1;

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  DDRD = 0;
  PORTD = 0;
  
  pinMode(Pin_CPU_Out_A, OUTPUT);
  pinMode(Pin_CPU_Out_B, OUTPUT);
#if !SQR_REV_A
  pinMode(Pin_CPU_Out_C, OUTPUT);
#endif
  pinMode(Pin_CPU_PWM_A, OUTPUT);
  pinMode(Pin_CPU_PWM_B, OUTPUT);
  pinMode(Pin_MUX_Out, INPUT);
  pinMode(Pin_MUX_Sel0, INPUT);
  pinMode(Pin_MUX_Sel1, INPUT);


  // CPU_PWM_A :: TIMER0 / PWM0 for percussive envelope, triggered by MUX_Partial_CD (INT0)
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  const byte pd = PIND;
  const bool cpu_a = 1 & ((pd >> BitD_SqrA_In) ^ (pd >> BitD_SqrB_In));
  const bool cpu_b = 1 & ((pd >> BitD_SqrC_In) ^ (pd >> BitD_SqrD_In));
  PORTA = cpu_a | (cpu_b << 1); //  note that PA2 is nRESET, but as that's set to be an input, this is fine

#if !SQR_REV_A
  const bool mux_sel1 = PINB & _BV(BitB_MUX_Sel1);
  const bool cpu_c = (mux_sel1 ? ((pd >> BitD_SqrA_In) & (pd >> BitD_SqrC_In)) : ((pd >> BitD_SqrB_In) & (pd >> BitD_SqrD_In)));
  if (cpu_c)
    PORTD |= BitD_CPU_Out_C;
  else
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
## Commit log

2026-05-17 importing
2026-06-23 squares: added revB board; added playground firmware
2026-06-23 squares: housekeeping moved playground fw
2026-06-28 [squares] updating playground. seems v crosstalky :(
2026-06-28 [squares] fixed up PIN_ macros so the pin mapping works...
2026-06-28 [squares] PCINT0 isr working
2026-06-29 [squares] PWM_A is now lil percussive env triggered by MUX_Sel0
2026-06-30 [squares] v1! added saw wave autotune to sqrC
